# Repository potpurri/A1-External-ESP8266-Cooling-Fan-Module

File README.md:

# ESP8266-based Fan Control for Bambu Lab A1 3D Printer

## Overview

This project showcases an ESP8266-based board designed to control an external fan to enhance nozzle and print cooling on the Bambu Lab A1 3D printer. The PCB consists of 4 layers in the stack-up: signals, ground, power, and signals.

**Note:** This project is a work in progress.

## Features

The board includes the following components:

- **ESP-12F module**: For wireless communication. The ESP-12F module allows the board to connect to a Wi-Fi network, enabling remote monitoring and control.
- **CH340C**: USB to UART converter for programming the ESP8266. It makes it easy to upload firmware updates or make changes to the program running on the ESP8266.
- **AM2320**: Digital temperature and humidity sensor. It provides accurate readings of the ambient temperature and humidity levels, which can be used to optimize the cooling process.
- **External LED connections**: To drive LEDs located on the printer. These LEDs can provide visual feedback, status indicators, or ambient lighting.
- **External fan connection**: For increased cooling. The fan helps enhance nozzle and print cooling, improving print quality by preventing overheating and warping.
- **PIR sensor connection**: Allows connecting a motion sensor to the board. It can detect motion and be used for various purposes, such as turning on the fan or LEDs when motion is detected near the printer.
- **Buck converter (LM2596)**: Used to step down the voltage from 24V to 5V. This is necessary because the printer's power supply typically provides 24V, but the board components require lower voltage levels to operate safely.
- **AMS1117**: Voltage regulator that further steps down the voltage from 5V to 3.3V, ensuring the ESP-12F module operates properly without being damaged.

## Images

Below are images of the PCB:

3D render of the front view of the PCB

3D render of the back view of the PCB

Front view of the actual PCB

Ground layer of the PCB stack-up

Power layer of the PCB stack-up

Back view of the PCB

## Schematics

For detailed schematics, please refer to the [schematic PDF](imgs/schematic.pdf).

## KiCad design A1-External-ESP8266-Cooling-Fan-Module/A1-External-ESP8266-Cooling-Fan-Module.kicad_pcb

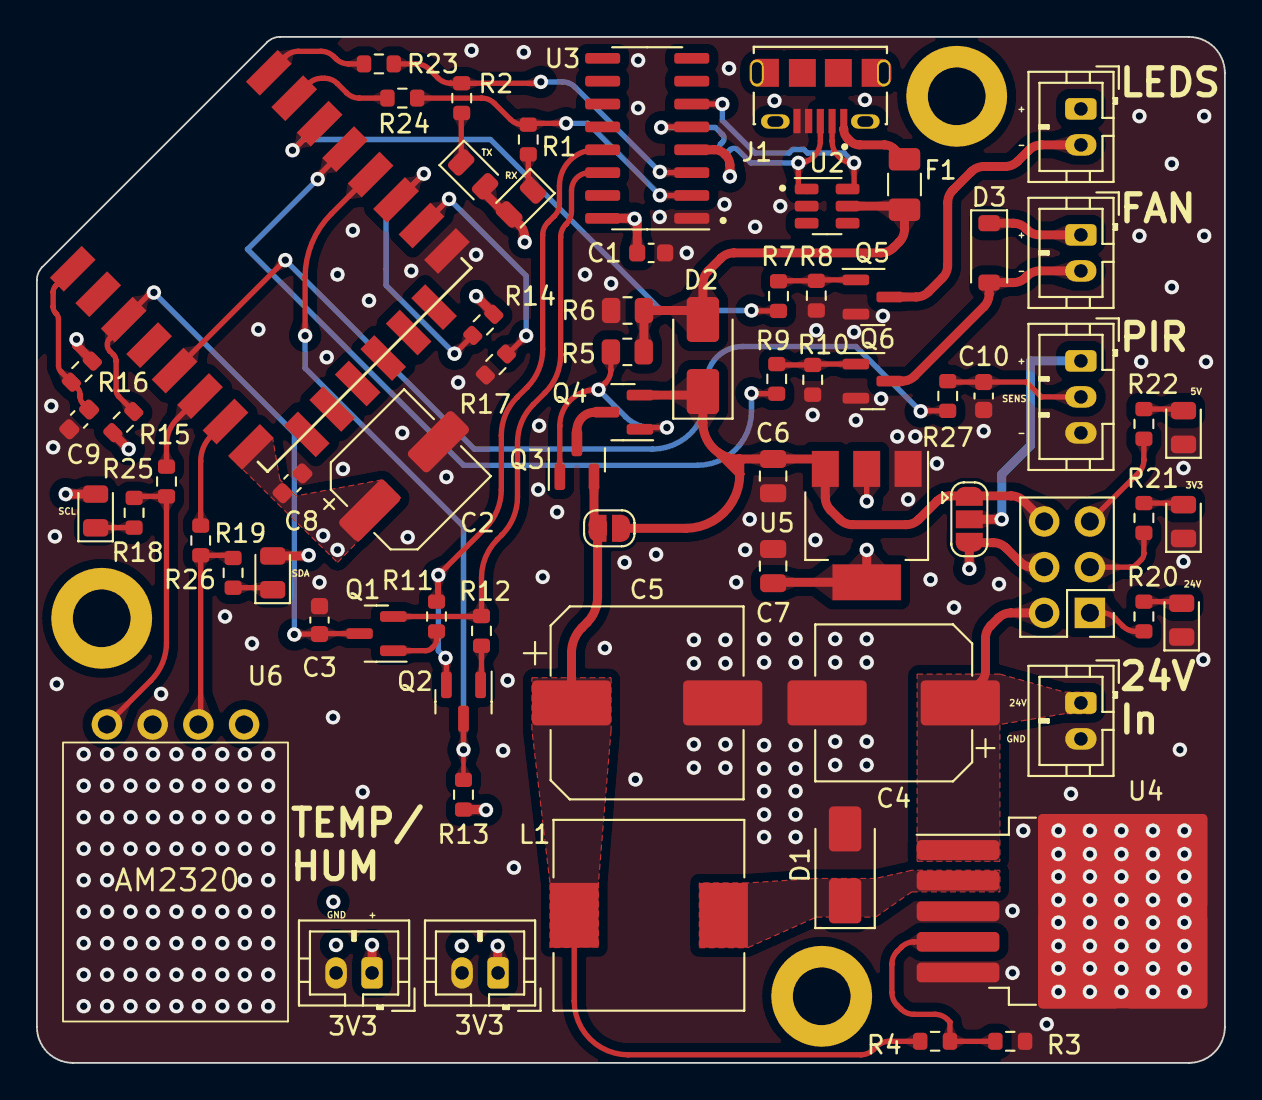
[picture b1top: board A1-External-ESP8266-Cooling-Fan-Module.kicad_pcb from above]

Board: 4 copper layers, 66.0 x 57.0 mm, 74 parts (0 on the bottom side), 49 nets.

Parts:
C1, C8, C10: 100n; C_0603_1608Metric
C2: 100u; CP_Elec_6.3x7.7
C3: 1u; C_0603_1608Metric
C4: 100u; CP_Elec_8x10.5
C5: 220u; CP_Elec_10x10.5
C6, C7: 10u; C_0805_2012Metric
C9: 470p; C_0603_1608Metric
D1, D2: SS34; D_SMA
D3: 1N4148; D_SOD-123
D4, D5, D6, D7, D8, D9, D10: LED; LED_0805_2012Metric
F1: 1A5; Fuse_1206_3216Metric
H1, H2, H3: MountingHole; MountingHole_3.2mm_M3_DIN965_Pad
J1: USB_B_Micro; AMPHENOL_10118194-0001LF
J2: Fan connector; JST_PH_B2B-PH-K_1x02_P2.00mm_Vertical
J3: Leds connector; JST_PH_B2B-PH-K_1x02_P2.00mm_Vertical
J4: PIR sensor; JST_PH_B3B-PH-K_1x03_P2.00mm_Vertical
J5: 24V IN; JST_PH_B2B-PH-K_1x02_P2.00mm_Vertical
J6, J8: 3V3 OUT; JST_PH_B2B-PH-K_1x02_P2.00mm_Vertical
J7: LEDS; PinHeader_2x03_P2.54mm_Vertical
JP1: SolderJumper_3_Open; SolderJumper-3_P1.3mm_Open_RoundedPad1.0x1.5mm
JP2: Cutoff bypass; SolderJumper-2_P1.3mm_Open_RoundedPad1.0x1.5mm
L1: 330m; L_10.4x10.4_H4.8
Q1, Q2, Q5, Q6: SI2300; SI2300 SOT-23
Q3, Q4: SI2301; SOT-23
R1, R2, R18, R19: 1k; R_0603_1608Metric
R3: 1k2; R_0603_1608Metric
R4: 3k9; R_0603_1608Metric
R5: 1k; R_0805_2012Metric
R6: 10k; R_0805_2012Metric
R7, R9, R11, R12, R23, R24, R25, R26, R27: 0; R_0603_1608Metric
R8, R10, R13, R14, R15, R16, R17: 10k; R_0603_1608Metric
R20: 2k2; R_0603_1608Metric
R21: 130; R_0603_1608Metric
R22: 300; R_0603_1608Metric
U1: ESP12-F; ESP-12E_SMD
U2: SRV05-4; SOT-23-6
U3: CH340C; SOIC-16_3.9x9.9mm_P1.27mm
U4: LM2596S-ADJ; TO-263-5_TabPin3
U5: AMS1117-3.3; SOT-223-3_TabPin2
U6: AM2320

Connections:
+3.3V: C1.1, C2.1, C7.1, C8.1, D7.2 (A), D8.2 (A), D9.2 (A), D10.2 (A), J6.1, J7.4, J8.1, JP1.3 (B), R13.2, R14.2, R15.2, R16.2, U1.8 (VCC), U3.4 (V3), U3.16 (VCC), U5.2 (VO), U6.1 (VDD)
+5V: C6.1, D2.1 (K), J7.6, JP1.1 (A), JP2.2 (B), Q4.2 (S), U5.3 (VI)
+24V: C4.1, D3.1 (K), J2.1, J3.1, J5.1, J7.2, U4.1 (VIN)
/D+: J1.3 (D+), U2.1 (IO1), U3.5 (UD+)
/D-: J1.2 (D-), U2.6 (IO4), U3.6 (UD-)
/FB: R3.2, R4.1, U4.4 (FB)
/LM2596-OUT: C5.1, JP2.1 (A), L1.2, Q3.2 (S), R4.2
/OUT: D1.1 (K), L1.1, U4.2 (OUT)
/SCL: R25.1, U1.6 (GPIO12)
/SDA: R26.1, U1.7 (GPIO13)
ESP_EN: C3.1, Q1.1 (D), R15.1, U1.3 (CH_PD)
ESP_GPIO0: Q2.1 (D), R13.1, U1.12 (GPIO0)
ESP_GPIO2: R14.1, U1.11 (GPIO2)
ESP_GPIO15: R17.1, U1.10 (GPIO15)
ESP_PIR-SENS: R27.2, U1.5 (GPIO14)
ESP_PWM-FAN: R9.2, U1.13 (GPIO4)
ESP_PWM-LEDS: R7.2, U1.14 (GPIO5)
ESP_RST: C9.1, R16.1, U1.1 (REST)
ESP_RXD: R1.2, R24.1, U3.2 (TXD)
ESP_TXD: R2.2, R23.1, U3.3 (RXD)
GND: C1.2, C2.2, C3.2, C4.2, C5.2, C6.2, C7.2, C8.2, C9.2, C10.2, D1.2 (A), D4.1 (K), D5.1 (K), D6.1 (K), J1.4 (ID), J1.5 (GND), J4.3, J5.2, J6.2, J8.2, Q5.3 (S), Q6.3 (S), R3.1, R6.2, R8.2, R10.2, R17.2, U1.9 (GND), U2.2 (VN), U3.1 (GND), U4.3 (GND), U4.5 (~ON/OFF), U5.1 (GND), U6.3 (GND)
unnamed: D3.2 (A), J2.2, Q6.1 (D)
unnamed: D4.2 (A), R20.2
unnamed: D5.2 (A), R21.2
unnamed: D6.2 (A), R22.2
unnamed: D7.1 (K), R19.1
unnamed: D8.1 (K), R18.1
unnamed: D9.1 (K), R1.1
unnamed: D10.1 (K), R2.1
unnamed: F1.1, J1.1 (VBUS)
unnamed: J3.2, Q5.1 (D)
unnamed: J4.1, JP1.2 (C)
unnamed: C10.1, J4.2, R27.1
unnamed: J7.1, R20.1
unnamed: J7.3, R21.1
unnamed: J7.5, R22.1
unnamed: Q1.2 (G), R11.2
unnamed: Q1.3 (S), R12.1, U3.14 (~RTS)
unnamed: Q2.2 (G), R12.2
unnamed: Q2.3 (S), R11.1, U3.13 (~DTR)
unnamed: Q3.3 (D), Q4.3 (D)
unnamed: Q3.1 (G), Q4.1 (G), R5.1
unnamed: Q5.2 (G), R7.1, R8.1
unnamed: Q6.2 (G), R9.1, R10.1
unnamed: R24.2, U1.15 (RXD)
unnamed: R23.2, U1.16 (TXD)
unnamed: R18.2, R25.2, U6.4 (SCL)
unnamed: R19.2, R26.2, U6.2 (SDA)
VBUS: D2.2 (A), F1.2, R5.2, R6.1, U2.5 (VP)

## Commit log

2025-01-12 USB to UART, Power Supply Circuit
2025-01-14 fixed 3.3v to ch340 chip
2025-01-19 finished schematic?
2025-02-18 final layout
2025-02-18 added images
2025-02-19 schematic
2025-02-19 changed img sizes
2025-02-19 fixed some text
2025-02-19 fixed readme
2025-02-19 readme fix
